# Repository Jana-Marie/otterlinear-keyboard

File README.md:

# otterlinear-keyboard

Just a smol ortholinear keyboard desgined by an otter for otters. It is built upon an STM32f042, Kailh Choc switches, featuring a Type-C jack and a wooden base. The keyboard measures only 214x84x17mm and has a smol, slim and chic design to fulfill its purpose as tv keyboard for my living room :3

The board itself can be ordered from JLCPCB with all parts populated (if available..), keycaps can be acquired e.g. via AliExpress. The design was focused both on a clean and minimal appearance, and a clean board layout with just the necessary parts.

### Status
 - **HW:** 100%
 - **FW:** 60%

### To-do
 - Finish firmware
   - Write keyboard layout mapper
   - find an easy way to map a new layout

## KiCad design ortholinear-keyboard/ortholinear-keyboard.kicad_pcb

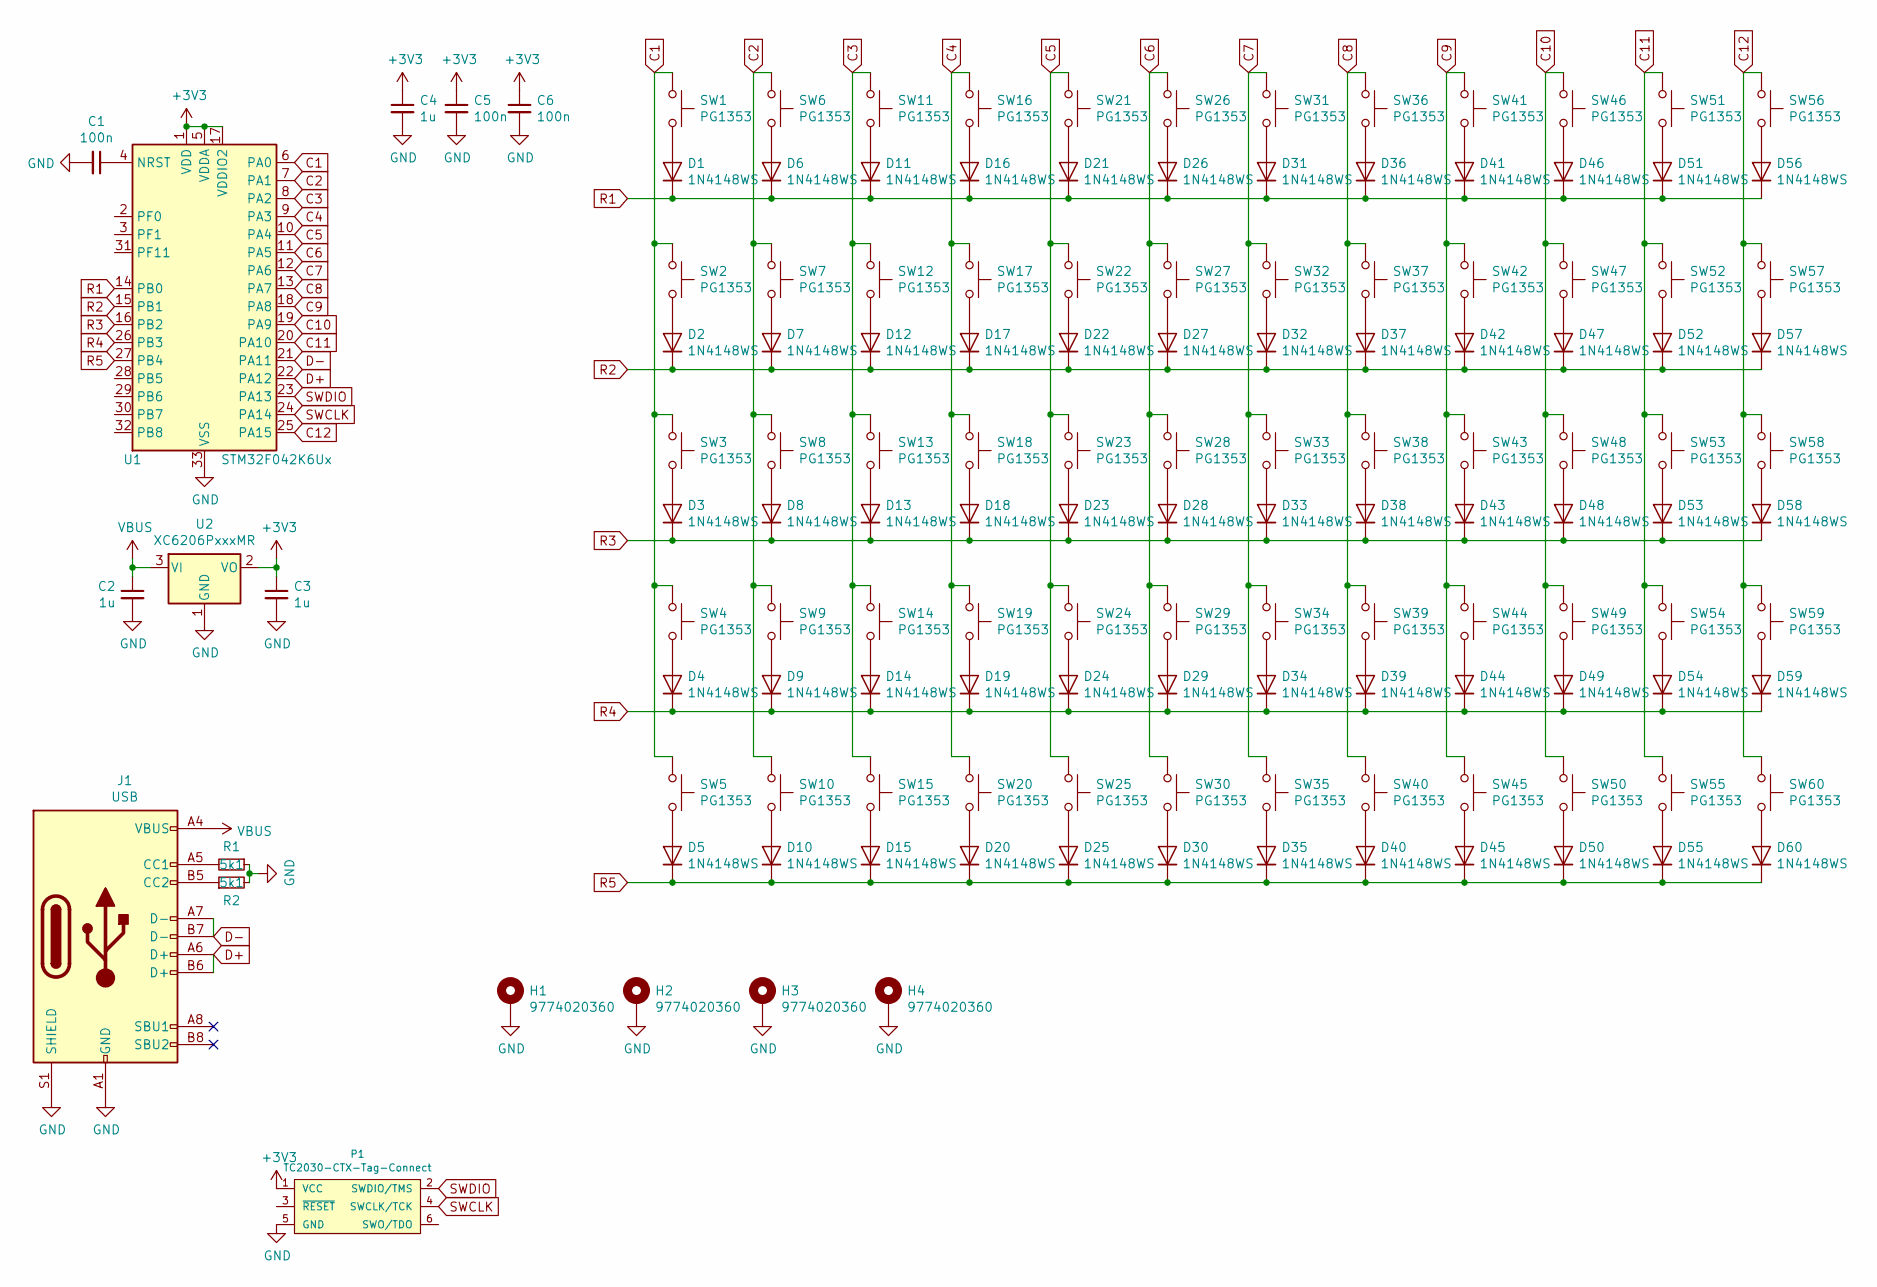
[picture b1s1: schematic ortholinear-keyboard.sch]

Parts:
C1, C5, C6: 100n; C_0402
C2, C3, C4: 1u; C_0402
D1, D2, D3, D4, D5, D6, D7, D8, D9, D10, D11, D12, D13, D14, D15, D16, D17, D18, D19, D20, D21, D22, D23, D24, D25, D26, D27, D28, D29, D30, D31, D32, D33, D34, D35, D36, D37, D38, D39, D40, D41, D42, D43, D44, D45, D46, D47, D48, D49, D50, D51, D52, D53, D54, D55, D56, D57, D58, D59, D60: 1N4148WS; D_SOD-323
H1, H2, H3, H4: 9774020360
J1: USB; USB-C 16Pin
P1: TC2030-CTX-Tag-Connect; TC2030
R1, R2: 5k1; R_0402
SW1, SW2, SW3, SW4, SW5, SW6, SW7, SW8, SW9, SW10, SW11, SW12, SW13, SW14, SW15, SW16, SW17, SW18, SW19, SW20, SW21, SW22, SW23, SW24, SW25, SW26, SW27, SW28, SW29, SW30, SW31, SW32, SW33, SW34, SW35, SW36, SW37, SW38, SW39, SW40, SW41, SW42, SW43, SW44, SW45, SW46, SW47, SW48, SW49, SW50, SW51, SW52, SW53, SW54, SW55, SW56, SW57, SW58, SW59, SW60: PG1353
U1: STM32F042K6Ux; QFN-32-1EP_5x5mm_P0.5mm_EP3.45x3.45mm
U2: XC6206PxxxMR; SOT-23

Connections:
+3V3: C3.1, C4.1, C5.1, C6.1, P1.1 (VCC), U1.1 (VDD), U1.5 (VDDA), U1.17 (VDDIO2), U2.2 (VO)
C1: SW1.1, SW2.1, SW3.1, SW4.1, SW5.1, U1.6 (PA0)
C2: SW6.1, SW7.1, SW8.1, SW9.1, SW10.1, U1.7 (PA1)
C3: SW11.1, SW12.1, SW13.1, SW14.1, SW15.1, U1.8 (PA2)
C4: SW16.1, SW17.1, SW18.1, SW19.1, SW20.1, U1.9 (PA3)
C5: SW21.1, SW22.1, SW23.1, SW24.1, SW25.1, U1.10 (PA4)
C6: SW26.1, SW27.1, SW28.1, SW29.1, SW30.1, U1.11 (PA5)
C7: SW31.1, SW32.1, SW33.1, SW34.1, SW35.1, U1.12 (PA6)
C8: SW36.1, SW37.1, SW38.1, SW39.1, SW40.1, U1.13 (PA7)
C9: SW41.1, SW42.1, SW43.1, SW44.1, SW45.1, U1.18 (PA8)
C10: SW46.1, SW47.1, SW48.1, SW49.1, SW50.1, U1.19 (PA9)
C11: SW51.1, SW52.1, SW53.1, SW54.1, SW55.1, U1.20 (PA10)
C12: SW56.1, SW57.1, SW58.1, SW59.1, SW60.1, U1.25 (PA15)
D+: J1.A6 (D+), J1.B6 (D+), U1.22 (PA12)
D-: J1.A7 (D-), J1.B7 (D-), U1.21 (PA11)
GND: C1.2, C2.2, C3.2, C4.2, C5.2, C6.2, H1.1, H2.1, H3.1, H4.1, J1.A1 (GND), J1.A12 (GND), J1.B1 (GND), J1.B12 (GND), J1.S1 (SHIELD), P1.5 (GND), R1.1, R2.2, U1.33 (VSS), U2.1 (GND)
unnamed: C1.1, U1.4 (NRST)
unnamed: D1.2 (A), SW1.2
unnamed: D2.2 (A), SW2.2
unnamed: D3.2 (A), SW3.2
unnamed: D4.2 (A), SW4.2
unnamed: D5.2 (A), SW5.2
unnamed: D6.2 (A), SW6.2
unnamed: D7.2 (A), SW7.2
unnamed: D8.2 (A), SW8.2
unnamed: D9.2 (A), SW9.2
unnamed: D10.2 (A), SW10.2
unnamed: D11.2 (A), SW11.2
unnamed: D12.2 (A), SW12.2
unnamed: D13.2 (A), SW13.2
unnamed: D14.2 (A), SW14.2
unnamed: D15.2 (A), SW15.2
unnamed: D16.2 (A), SW16.2
unnamed: D17.2 (A), SW17.2
unnamed: D18.2 (A), SW18.2
unnamed: D19.2 (A), SW19.2
unnamed: D20.2 (A), SW20.2
unnamed: D21.2 (A), SW21.2
unnamed: D22.2 (A), SW22.2
unnamed: D23.2 (A), SW23.2
unnamed: D24.2 (A), SW24.2
unnamed: D25.2 (A), SW25.2
unnamed: D26.2 (A), SW26.2
unnamed: D27.2 (A), SW27.2
unnamed: D28.2 (A), SW28.2
unnamed: D29.2 (A), SW29.2
unnamed: D30.2 (A), SW30.2
unnamed: D31.2 (A), SW31.2
unnamed: D32.2 (A), SW32.2
unnamed: D33.2 (A), SW33.2
unnamed: D34.2 (A), SW34.2
unnamed: D35.2 (A), SW35.2
unnamed: D36.2 (A), SW36.2
unnamed: D37.2 (A), SW37.2
unnamed: D38.2 (A), SW38.2
unnamed: D39.2 (A), SW39.2
unnamed: D40.2 (A), SW40.2
unnamed: D41.2 (A), SW41.2
unnamed: D42.2 (A), SW42.2
unnamed: D43.2 (A), SW43.2
unnamed: D44.2 (A), SW44.2
unnamed: D45.2 (A), SW45.2
unnamed: D46.2 (A), SW46.2
unnamed: D47.2 (A), SW47.2
unnamed: D48.2 (A), SW48.2
unnamed: D49.2 (A), SW49.2
unnamed: D50.2 (A), SW50.2
unnamed: D51.2 (A), SW51.2
unnamed: D52.2 (A), SW52.2
unnamed: D53.2 (A), SW53.2
unnamed: D54.2 (A), SW54.2
unnamed: D55.2 (A), SW55.2
unnamed: D56.2 (A), SW56.2
unnamed: D57.2 (A), SW57.2
unnamed: D58.2 (A), SW58.2
unnamed: D59.2 (A), SW59.2
unnamed: D60.2 (A), SW60.2
unnamed: J1.A5 (CC1), R1.2
unnamed: J1.B5 (CC2), R2.1
R1: D1.1 (K), D6.1 (K), D11.1 (K), D16.1 (K), D21.1 (K), D26.1 (K), D31.1 (K), D36.1 (K), D41.1 (K), D46.1 (K), D51.1 (K), D56.1 (K), U1.14 (PB0)
R2: D2.1 (K), D7.1 (K), D12.1 (K), D17.1 (K), D22.1 (K), D27.1 (K), D32.1 (K), D37.1 (K), D42.1 (K), D47.1 (K), D52.1 (K), D57.1 (K), U1.15 (PB1)
R3: D3.1 (K), D8.1 (K), D13.1 (K), D18.1 (K), D23.1 (K), D28.1 (K), D33.1 (K), D38.1 (K), D43.1 (K), D48.1 (K), D53.1 (K), D58.1 (K), U1.16 (PB2)
R4: D4.1 (K), D9.1 (K), D14.1 (K), D19.1 (K), D24.1 (K), D29.1 (K), D34.1 (K), D39.1 (K), D44.1 (K), D49.1 (K), D54.1 (K), D59.1 (K), U1.26 (PB3)
R5: D5.1 (K), D10.1 (K), D15.1 (K), D20.1 (K), D25.1 (K), D30.1 (K), D35.1 (K), D40.1 (K), D45.1 (K), D50.1 (K), D55.1 (K), D60.1 (K), U1.27 (PB4)
SWCLK: P1.4 (SWCLK/TCK), U1.24 (PA14)
SWDIO: P1.2 (SWDIO/TMS), U1.23 (PA13)
VBUS: C2.1, J1.A4 (VBUS), J1.A9 (VBUS), J1.B4 (VBUS), J1.B9 (VBUS), U2.3 (VI)

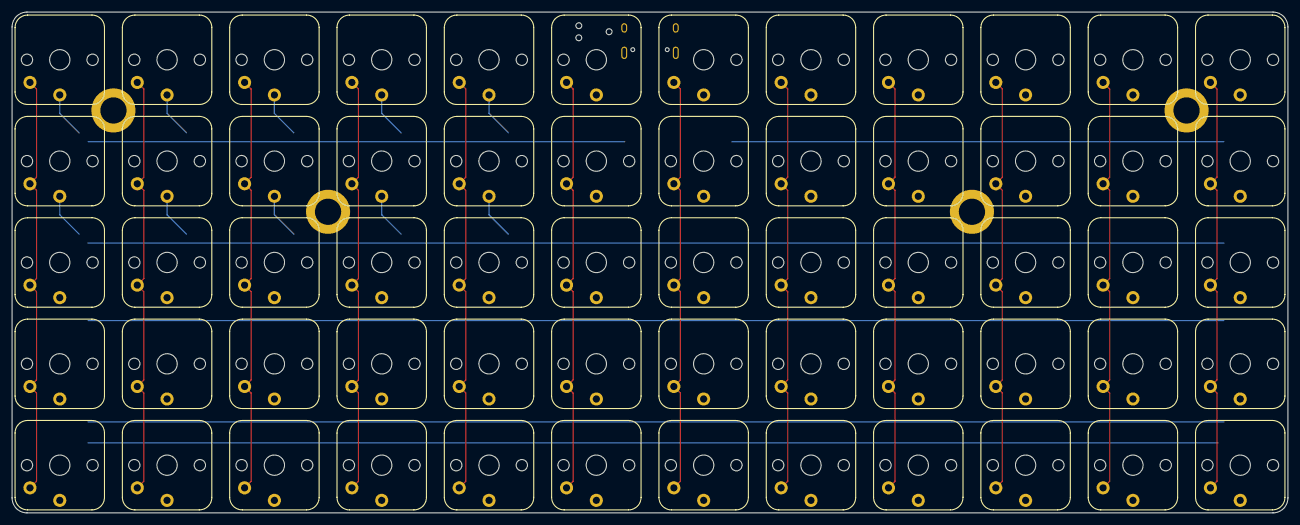
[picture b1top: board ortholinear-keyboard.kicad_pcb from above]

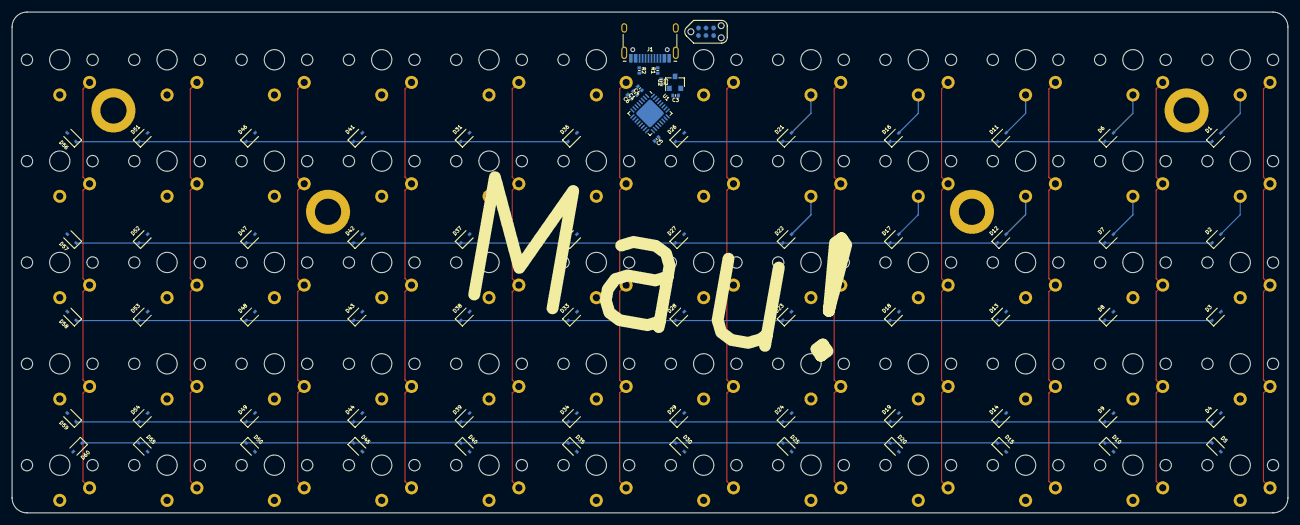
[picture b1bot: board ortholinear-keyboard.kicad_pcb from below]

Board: 2 copper layers, 214.0 x 84.0 mm, 136 parts (76 on the bottom side), 87 nets.

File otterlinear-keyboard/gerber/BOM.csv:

Comment,Designator,Footprint,LCSC
100n,"C1,C5,C6",otter:C_0402,C1525
1u,"C2,C3,C4",otter:C_0402,C52923
1N4148WS,"D56,D51,D46,D41,D36,D31,D26,D21,D16,D11,D6,D1,D57,D52,D47,D42,D37,D32,D27,D22,D17,D12,D7,D2,D58,D53,D48,D43,D38,D33,D28,D23,D18,D13,D8,D3,D59,D54,D49,D44,D39,D34,D29,D24,D19,D14,D9,D4,D60,D55,D50,D45,D40,D35,D30,D25,D20,D15,D10,D5",Diode_SMD:D_SOD-323,C2128
SP0502BAHT,D61,Package_TO_SOT_SMD:SOT-23,C32677
9774020360,"H2,H1,H3,H4",otter:9774020360,DNP
USB,J1,otter:USB-C 16Pin,C393939
TC2030-CTX-Tag-Connect,P1,otter:TC2030,DNP
5k1,"R1,R2",otter:R_0402,C25905
PG1353,"SW56,SW51,SW46,SW41,SW36,SW31,SW26,SW21,SW16,SW11,SW6,SW1,SW57,SW52,SW47,SW42,SW37,SW32,SW27,SW22,SW17,SW12,SW7,SW2,SW58,SW53,SW48,SW43,SW38,SW33,SW28,SW23,SW18,SW13,SW8,SW3,SW59,SW54,SW49,SW44,SW39,SW34,SW29,SW24,SW19,SW14,SW9,SW4,SW60,SW55,SW50,SW45,SW40,SW35,SW30,SW25,SW20,SW15,SW10,SW5",otter:PG1353,DNP
STM32F042K6Ux,U1,Package_DFN_QFN:QFN-32-1EP_5x5mm_P0.5mm_EP3.45x3.45mm,C110616
XC6206PxxxMR,U2,Package_TO_SOT_SMD:SOT-23,C5446

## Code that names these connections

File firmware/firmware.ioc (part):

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Mcu.Name=STM32F042K(4-6)Ux
Mcu.Package=UFQFPN32
Mcu.UserName=STM32F042K6Ux
PA0.GPIOParameters=GPIO_PuPd,GPIO_Label
PA0.GPIO_Label=IN_C6
PA0.GPIO_PuPd=GPIO_PULLDOWN
PA0.Signal=GPIO_Input
PA1.GPIOParameters=GPIO_PuPd,GPIO_Label
PA1.GPIO_Label=IN_C5
PA1.GPIO_PuPd=GPIO_PULLDOWN
PA1.Signal=GPIO_Input
PA10.GPIOParameters=GPIO_PuPd,GPIO_Label
PA10.GPIO_Label=IN_C8
PA10.GPIO_PuPd=GPIO_PULLDOWN
PA10.Signal=GPIO_Input
PA11.Mode=Device
PA11.Signal=USB_DM
PA12.Mode=Device
PA12.Signal=USB_DP
PA13.Mode=Serial_Wire
PA13.Signal=SYS_SWDIO
PA14.Mode=Serial_Wire
PA14.Signal=SYS_SWCLK
PA15.GPIOParameters=GPIO_PuPd,GPIO_Label
PA15.GPIO_Label=IN_C7
PA15.GPIO_PuPd=GPIO_PULLDOWN
PA15.Signal=GPIO_Input
PA2.GPIOParameters=GPIO_PuPd,GPIO_Label
PA2.GPIO_Label=IN_C4
PA2.GPIO_PuPd=GPIO_PULLDOWN
PA2.Signal=GPIO_Input
PA3.GPIOParameters=GPIO_PuPd,GPIO_Label
PA3.GPIO_Label=IN_C3
PA3.GPIO_PuPd=GPIO_PULLDOWN
PA3.Signal=GPIO_Input
PA4.GPIOParameters=GPIO_PuPd,GPIO_Label
PA4.GPIO_Label=IN_C2
PA4.GPIO_PuPd=GPIO_PULLDOWN
PA4.Signal=GPIO_Input
PA5.GPIOParameters=GPIO_PuPd,GPIO_Label
PA5.GPIO_Label=IN_C1
PA5.GPIO_PuPd=GPIO_PULLDOWN
PA5.Signal=GPIO_Input
PA6.GPIOParameters=GPIO_PuPd,GPIO_Label
PA6.GPIO_Label=IN_C12
PA6.GPIO_PuPd=GPIO_PULLDOWN
PA6.Signal=GPIO_Input
PA7.GPIOParameters=GPIO_PuPd,GPIO_Label
PA7.GPIO_Label=IN_C11
PA7.GPIO_PuPd=GPIO_PULLDOWN
PA7.Signal=GPIO_Input
PA8.GPIOParameters=GPIO_PuPd,GPIO_Label
PA8.GPIO_Label=IN_C10
PA8.GPIO_PuPd=GPIO_PULLDOWN
PA8.Signal=GPIO_Input
PA9.GPIOParameters=GPIO_PuPd,GPIO_Label
PA9.GPIO_Label=IN_C9
PA9.GPIO_PuPd=GPIO_PULLDOWN
PA9.Signal=GPIO_Input
PB4.GPIOParameters=GPIO_Speed,GPIO_Label
PB4.GPIO_Label=OUT_R5
PB4.GPIO_Speed=GPIO_SPEED_FREQ_LOW
PB4.Signal=GPIO_Output
PB5.GPIOParameters=GPIO_Speed,GPIO_Label
PB5.GPIO_Label=OUT_R4
PB5.GPIO_Speed=GPIO_SPEED_FREQ_LOW
PB5.Signal=GPIO_Output
PB6.GPIOParameters=GPIO_Speed,GPIO_Label
PB6.GPIO_Label=OUT_R3
PB6.GPIO_Speed=GPIO_SPEED_FREQ_LOW
PB6.Signal=GPIO_Output
PB7.GPIOParameters=GPIO_Speed,GPIO_Label
PB7.GPIO_Label=OUT_R2
PB7.GPIO_Speed=GPIO_SPEED_FREQ_LOW
PB7.Signal=GPIO_Output
PB8.GPIOParameters=GPIO_Speed,GPIO_Label
PB8.GPIO_Label=OUT_R1
PB8.GPIO_Speed=GPIO_SPEED_FREQ_LOW
PB8.Signal=GPIO_Output
RCC.SYSCLKFreq_VALUE=48000000
RCC.SYSCLKSource=RCC_SYSCLKSOURCE_HSI48
board=custom

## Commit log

2021-05-18 fixed markdown
2021-05-18 initial design
2021-05-19 added layou
2021-05-19 exported production files
2021-05-19 updated production files
2021-06-10 updated board files
2021-09-07 added initial firmware
2021-09-08 moved firmware
2021-09-08 added tooling
2021-09-08 renamed folder
2021-09-08 added gitignoe
2021-09-08 added aligner design
2021-12-19 finished v1.0, renamed project, regenerated gerber
2021-12-19 initial firmware, boots, enumerates, thats it
2021-12-19 removed hid folder
2021-12-19 removed old files
2021-12-19 moved folder
2021-12-19 updated tooling
2021-12-19 added images
2021-12-30 initial firmware
